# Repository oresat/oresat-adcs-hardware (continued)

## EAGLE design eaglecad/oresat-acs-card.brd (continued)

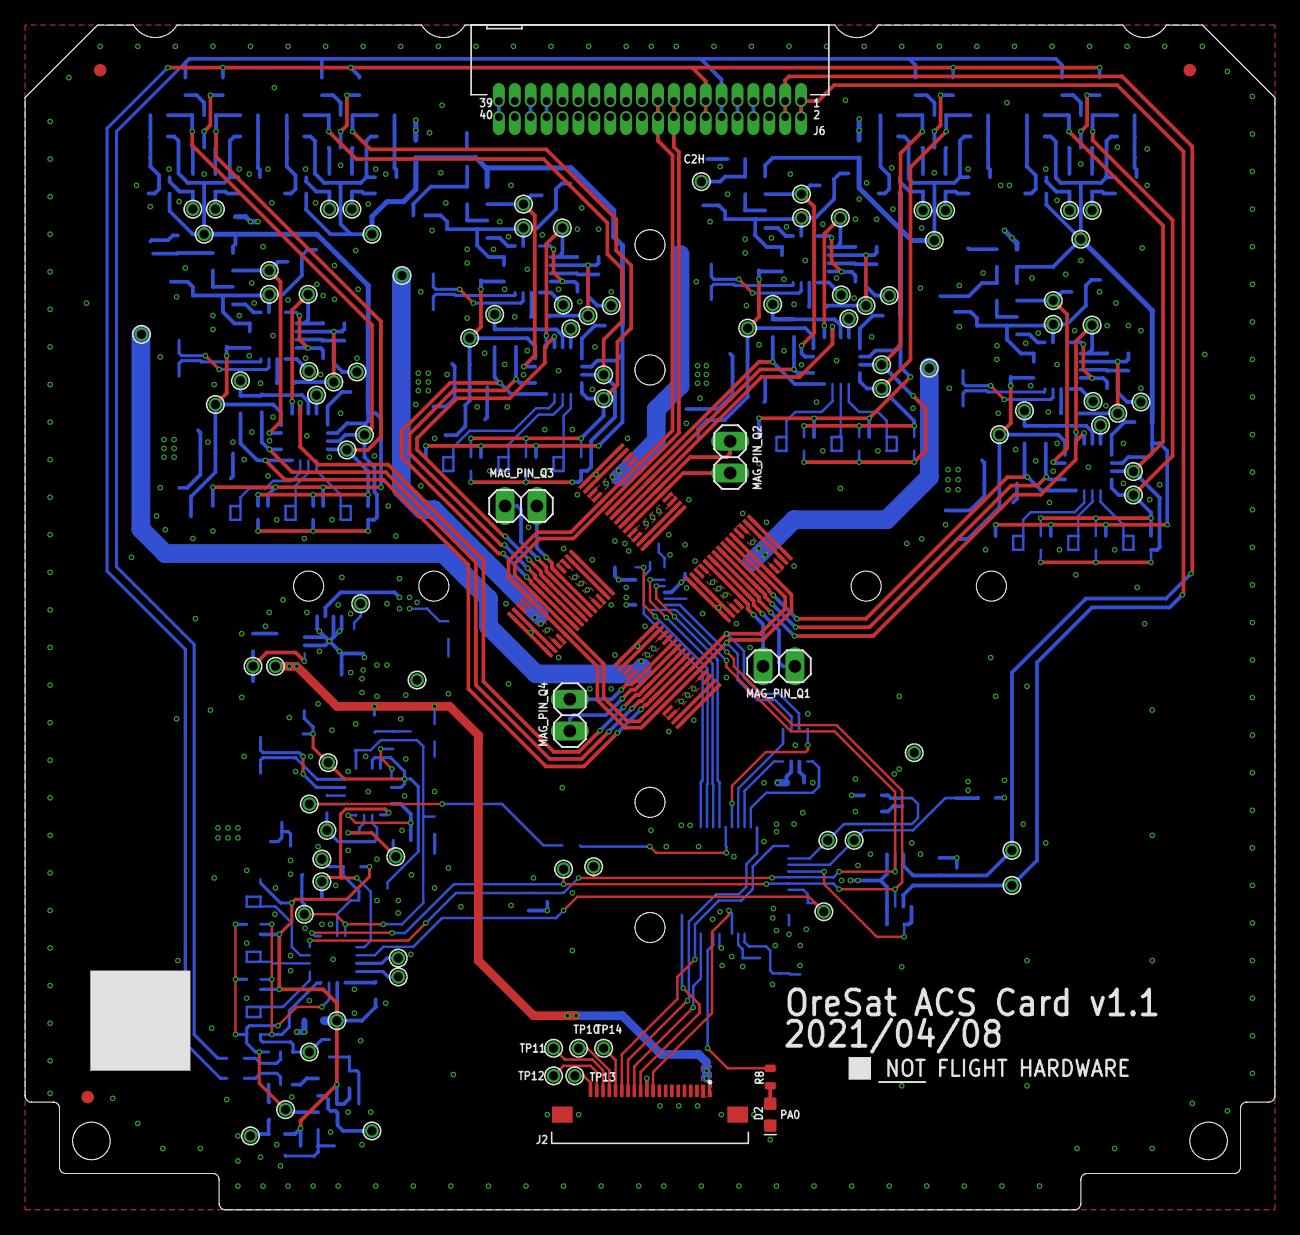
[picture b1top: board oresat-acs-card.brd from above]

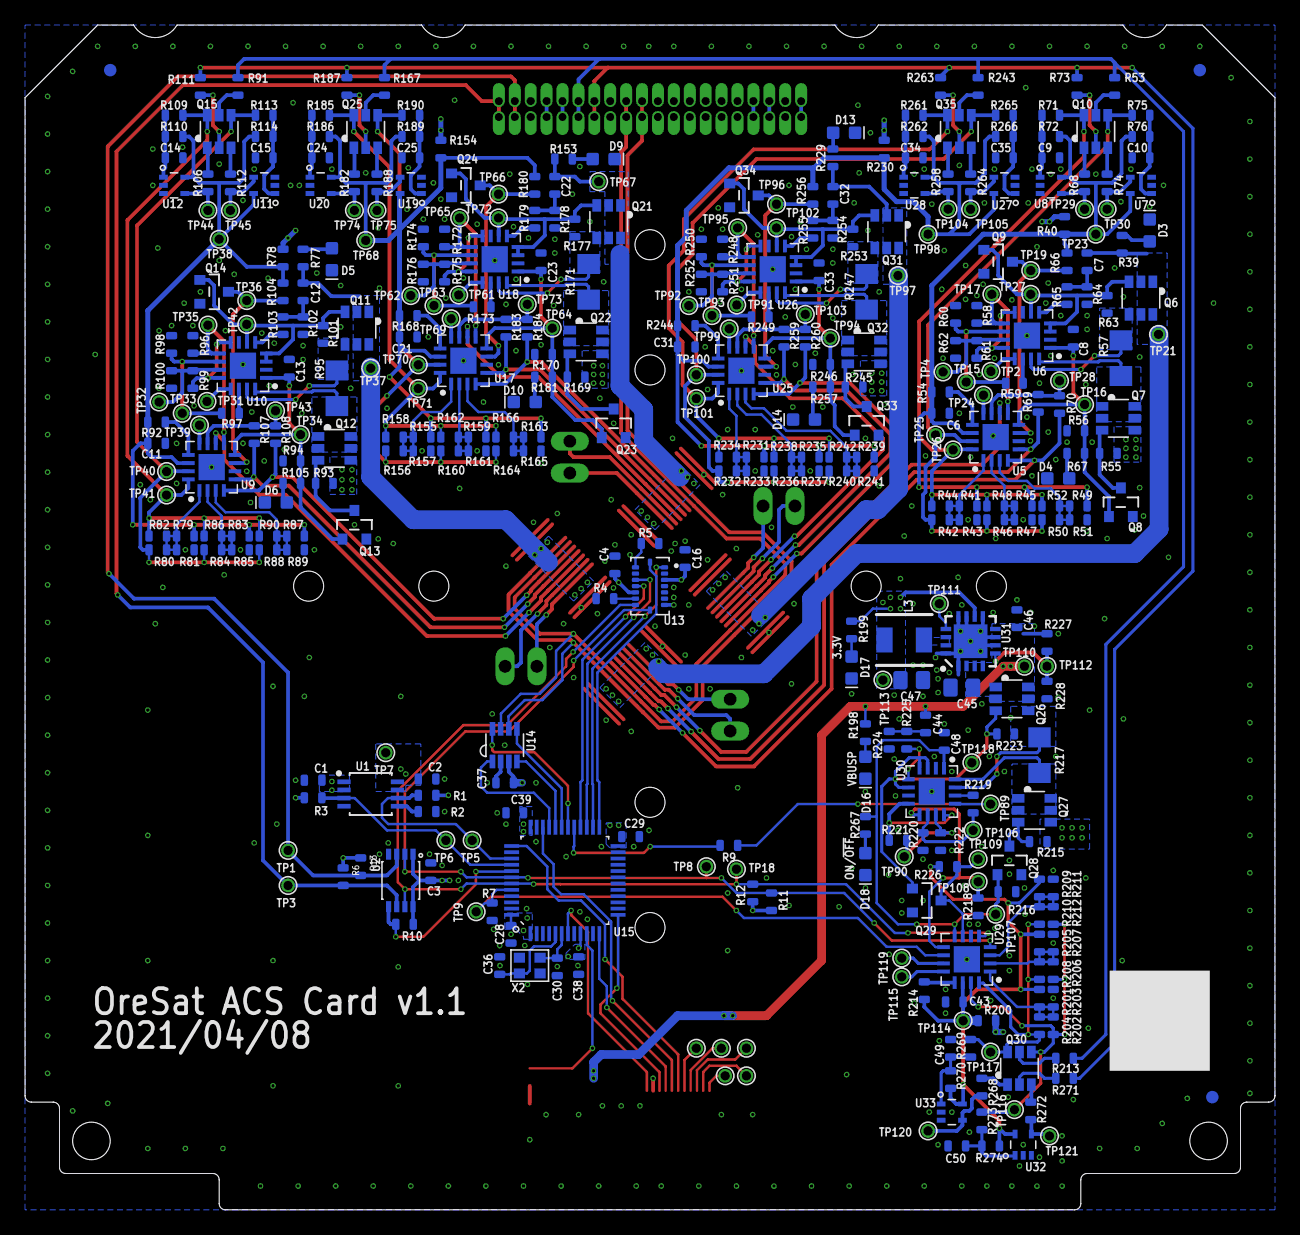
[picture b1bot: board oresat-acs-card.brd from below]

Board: 4 copper layers, 99.8 x 94.6 mm, 418 parts (389 on the bottom side), 242 nets.

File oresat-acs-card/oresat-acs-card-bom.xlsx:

Bill Of Materials for OreSat ACS Card
source file: oresat-acs-card.sch
Last modified: 2020/09/21
PCB version: 1.1 |  |  | P/DNP = | Place/Do Not Place (DNP is for final production boards)
BOM revision: 2 |  |  | Generic = | Any generic part with the same characteristics are OK (e.g., bypass cap)
Cnt | Part References | P/DNP | Mfg | Mfg PN | Description | Generic | DIS | DPN
10 | R59, R61, R97, R99, R173, R175, R219, R221, R249, R251 | P | Yageo | RC0603JR-070RL | RES SMD 0 OHM JUMPER 1/10W 0603 | Y | Digi-Key | 311-0.0GRCT-ND
5 | R40, R78, R154, R200, R230 | P | Yageo | RC0603FR-0710RL | RES SMD 10 OHM 1% 1/10W 0603 | Y | Digi-Key | 311-10.0HRCT-ND
10 | R53, R73, R91, R111, R167, R187, R213, R243, R263, R271 | P | Yageo | RC0603FR-07100RL | RES SMD 100 OHM 1% 1/10W 0603 | Y | Digi-Key | 311-100HRCT-ND
5 | R57, R95, R171, R217, R247 | P | Stackpole | CSR1206FTR100 | RES 0.1 OHM 1% 1/2W 1206 | Y | Digi-Key | CSR1206FTR100CT-ND
10 | C6, C11, C21, C28, C29, C31, C37, C38, C39, C43 | P | Samsung | CL10B104KB8NNNL | CAP CER 0.1UF 50V X7R 0603 | Y | Digi-Key | 1276-CL10B104KB8NNNLCT-ND
40 | R1, R3, R4, R5, R6, R7, R9, R10, R13, R54, R55, R56, R58, R63, R66, R92, R93, R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 | P | Yageo | RC0603FR-0710KL | RES SMD 10K OHM 1% 1/10W 0603 | Y | Digi-Key | 311-10.0KHRCT-ND
1 | C45 | P | Samsung | CL21B106KOQNNNG | CAP CER 10UF 16V X7R 0805 | Y | Digi-Key | 1276-6472-1-ND
1 | X2 | P | ECS Inc. | ECS-160-10-36Q-ES-TR | 16MHz ±30ppm Crystal 10pF 80 Ohms | Y | Digi-Key | XC2181CT-ND
10 | R72, R76, R110, R114, R186, R190, R262, R266, R270, R274 | P | Yageo | RC0603FR-071ML | RES SMD 1M OHM 1% 1/10W 0603 | Y | Digi-Key | 311-1.00MHRCT-ND
21 | C1, C2, C3, C4, C8, C9, C10, C13, C14, C15, C16, C23, C24, C25, C33, C34, C35, 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 | P | Yageo | CC0603KRX7R7BB105 | CAP CER 1UF 16V X7R 0603 | Y | Digi-Key | 311-1446-1-ND
14 | R8, R11, R12, R39, R67, R77, R105, R153, R181, R198, R199, R229, R257, R267 | P | TE Connectivity | CRGCQ0603F2K7 | RES CRGCQ 0603 2K7 1% | Y | Digi-Key | A129693CT-ND
2 | C30, C36 | P | Samsung | CL10C200JB8NNNC | CAP CER 20PF 50V C0G/NP0 0603 | Y | Digi-Key | 1276-1187-1-ND
1 | C47 | P | Murata | GRM21BD71A226ME44L | CAP CER 22UF 10V X7T 0805 | Y | Digi-Key | 490-9959-1-ND
1 | R2 | P | Yageo | RC0603FR-0723K7L | RES SMD 23.7K OHM 1% 1/10W 0603 | Y | Digi-Key | 311-23.7KHRCT-ND
10 | R71, R75, R109, R113, R185, R189, R261, R265, R269, R273 | P | Vishay | MCT06030C3303FP000 | RES SMD 330K OHM 1% 1/8W 0603 | Y | Digi-Key | 749-1638-1-ND
8 | R69, R70, R107, R108, R183, R184, R259, R260 | P | Yageo | RC0603FR-0747KL | RES SMD 47K OHM 1% 1/10W 0603 | Y | Digi-Key | 311-47.0KHRCT-ND
1 | L3 | P | ECS | ECS-MPI4040R4-6R8-R | FIXED IND 6.8UH 2.4A 91 MOHM SMD | N | Digi-Key | XC2337CT-ND
10 | R68, R74, R106, R112, R182, R188, R258, R264, R268, R272 | P | Yageo | RC0603FR-07665KL | RES SMD 665K OHM 1% 1/10W 0603 | Y | Digi-Key | 311-665KHRCT-ND
6 | D2, D4, D6, D10, D14, D18 | P | Inolux | IN-S63AT5A | LED AMBER CLEAR 0603 SMD | Y | Digi-Key | 1830-1064-1-ND
1 | U13 | P | Bosch Sensortec | BMI088 | ACCELEROMETER 16LGA | N | Digi-Key | 828-1082-1-ND
5 | Q10, Q15, Q25, Q30, Q35 | P | Diodes Inc | DMP2240UDM | MOSFET 2P-CH 20V 2A SOT-26 | N | Digi-Key | DMP2240UDMDICT-ND
6 | D3, D5, D9, D13, D16, D17 | P | Rohm | SML-E12M8WT86 | LED GREEN DIFFUSED 0603 SMD | Y | Digi-Key | 511-1584-1-ND
1 | J6 | P | Samtec | TFM-120-01-L-D-RA | J-SAMTEC-TFM-120-X1-XXX-D-RA | N | Digi-Key | SAM10145-ND
1 | U2 | P | Linear | LTC4300A-1IMS8#TRPBF | IC ACCELERATOR I2C HOTSWAP 8MSOP | N | Digi-Key | LTC4300A-1IMS8#TRPBFCT-ND
5 | U6, U10, U18, U26, U30 | P | Maxim | MAX4211FETE | Current Monitor Regulator High-Side 16-TQFN | N | Digi-Key | MAX4211FETE+-ND
5 | U5, U9, U17, U25, U29 | P | Maxim | MAX7310ATE | I/O Expander 8 I²C, SMBus 400kHz 16-TQFN | N | Digi-Key | MAX7310ATE+-ND
1 | U1 | P | Maxim | MAX892LEUA+ | Power Switch/Driver 1:1 P-Channel 250mA 8-uMAX | N | Digi-Key | MAX892LEUA+-ND
4 | QUADRANT1, QUADRANT2, QUADRANT3, QUADRANT4 | P | Molex | 0555600307 | 30 Position Connector Plug, Outer Shroud Contacts Surface Mount Gold | N | Digi-Key | WM9218CT-ND
10 | U7, U8, U11, U12, U19, U20, U27, U28, U32, U33 | P | Microchip | MIC842LYC5-TR | Comparator with Voltage Reference Push-Pull SC-70-5 | N | Digi-Key | 576-2927-1-ND
10 | Q6, Q7, Q11, Q12, Q21, Q22, Q26, Q27, Q31, Q32 | P | Diodes Inc | DMP3050LVT-7 | MOSFET-PCH-SOT23-6 | N | Digi-Key | DMP3050LVT-7DICT-ND
5 | C7, C12, C22, C32, C44 | NP |  |  | NP | Y
81 | R41, R42, R43, R44, R45, R46, R47, R48, R49, R50, R51, R52, R60, R62, R64, R65,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 | NP |  |  | NP | Y
1 | J2 | P | Wurth |  | ORESAT-DEBUG-CONNECTOR-SOLAR | N
10 | Q8, Q9, Q13, Q14, Q23, Q24, Q28, Q29, Q33, Q34 | P | Nexperia | PMV45EN2R | N-Channel 30V 4.1A (Ta) 510mW (Ta), 5W (Tc) Surface Mount TO-236AB | N | Digi-Key | 1727-2307-1-ND
1 | U15 | P | STMicroelectronics | STM32F042K6T7 | ARM® Cortex®-M0 STM32F0 Microcontroller | N | Digi-Key | 497-18516-ND
1 | U14 | P | Texas Instruments | TCAN330GDCNT | 1/1 Transceiver CANbus SOT-23-8 | N | Digi-Key | 296-44211-1-ND
1 | U31 | P | Texas Instruments | TPS62111RSAR | Buck Switching Regulator IC Positive Fixed 3.3V 1 Output 1.5A 16-VQFN Exposed P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 | N | Digi-Key | 296-37681-2-ND
VERSION INFO
 | Date | Notes
Rev
1.1r1 | 44095 | Changed 0402 components to 0603 and updated some values
1.1r0 | 44082 | BOM for 1.1r0
1.0r0 | 44036 | First BOM version

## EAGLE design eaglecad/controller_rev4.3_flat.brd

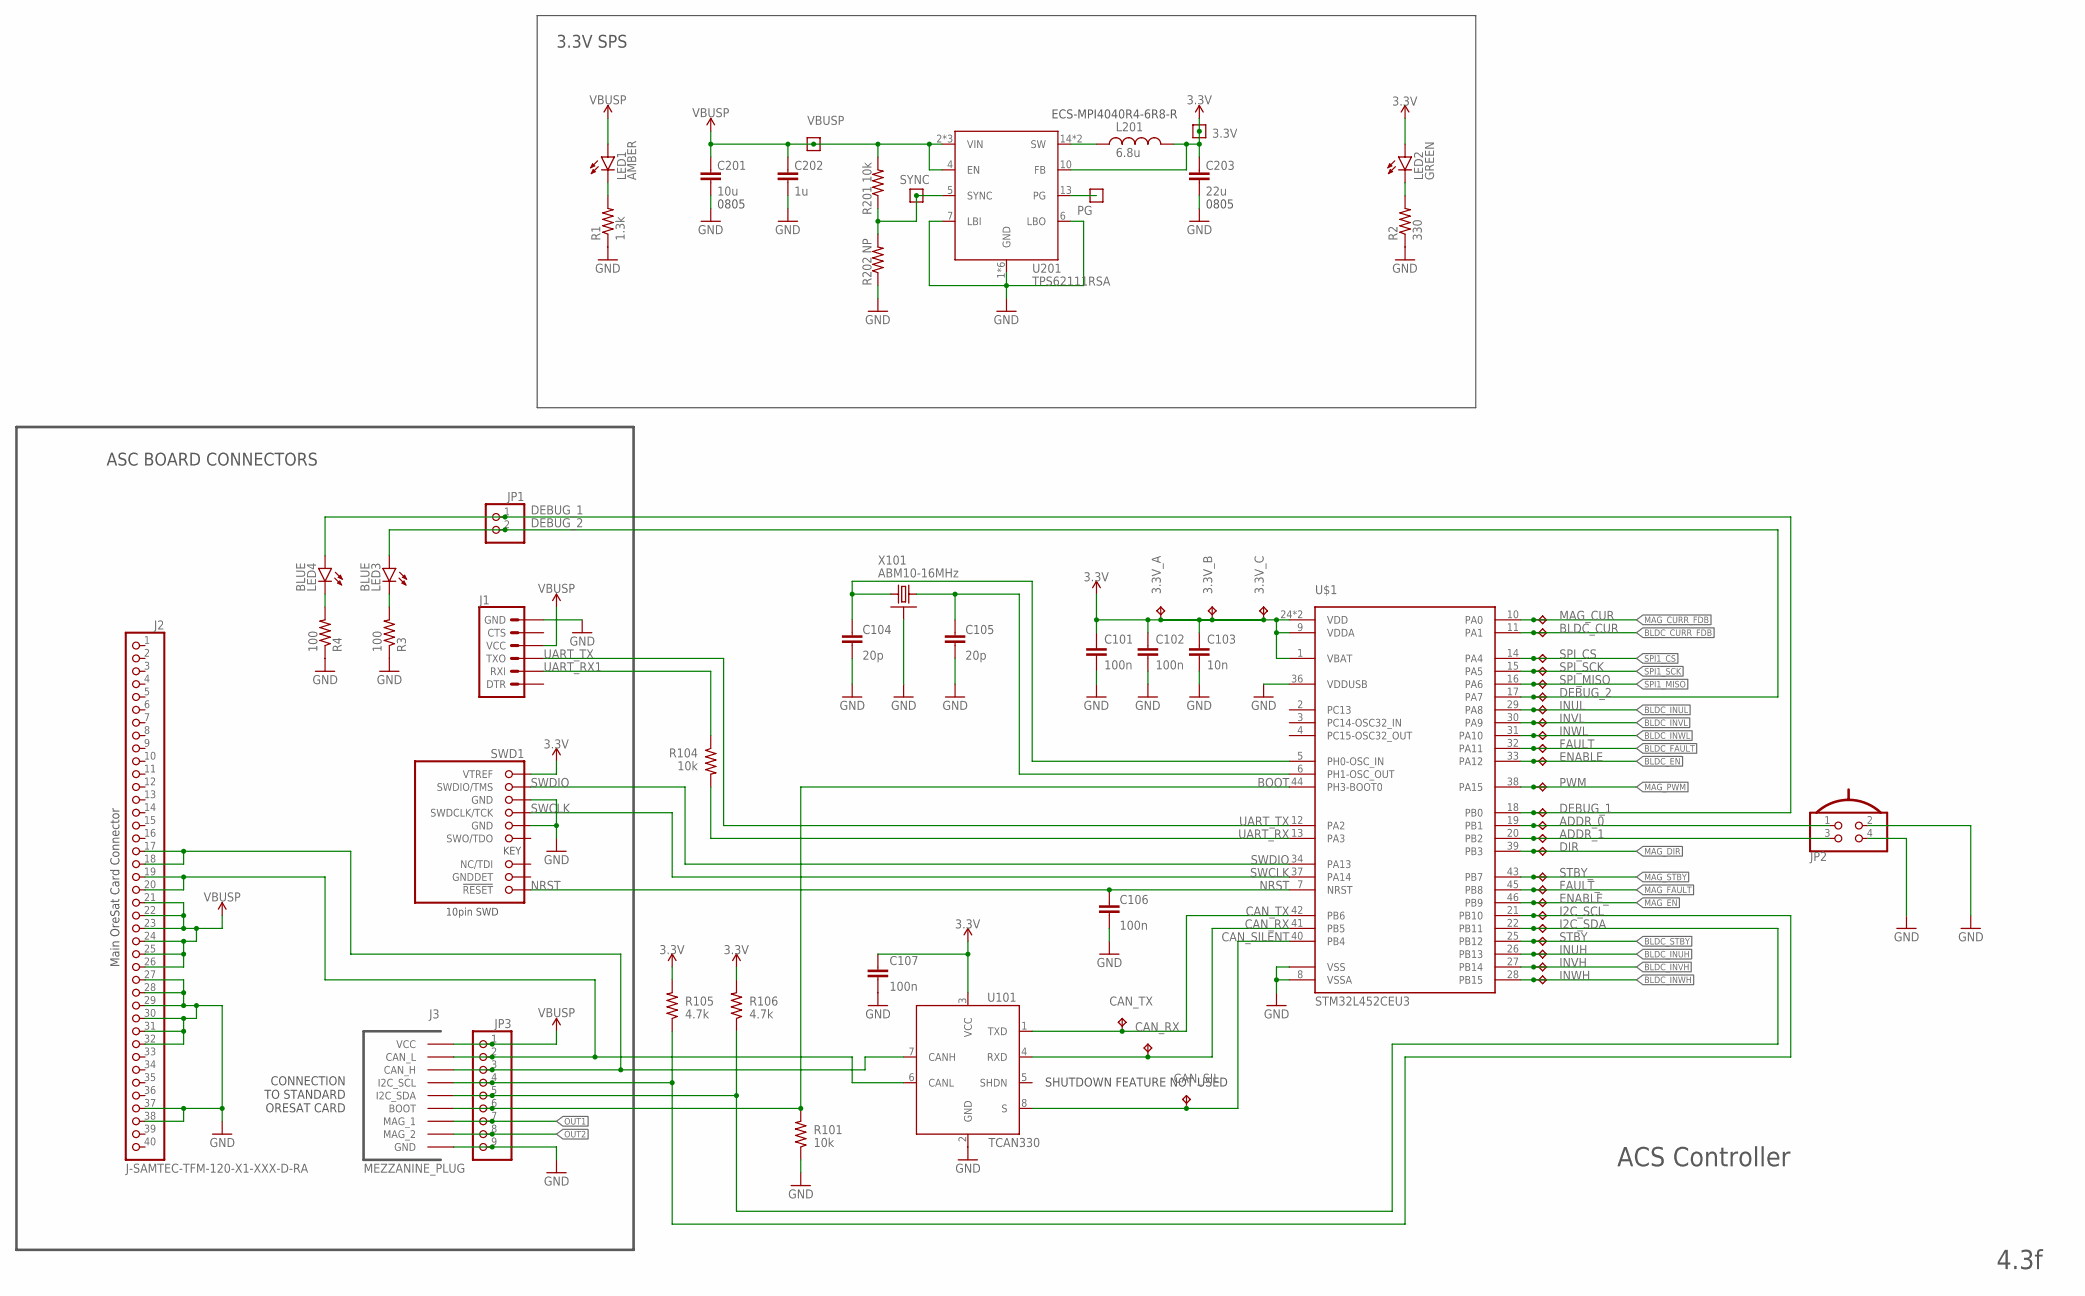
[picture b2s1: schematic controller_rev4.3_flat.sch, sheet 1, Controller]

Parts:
3.3V: TEST-POINT-LARGE-SQUARE; 1X01
3.3V_A, 3.3V_B, 3.3V_C: TEST-POINT-LARGE; 1X01
ADDR_0, ADDR_1: TEST-POINT-LARGE; 1X01
BLDC_CUR: TEST-POINT-LARGE; 1X01
C101, C102, C107: 100n; .0402-B-NOSILK; MPN CL05B104KO5NNNC
C103: 10n; .0402-B-NOSILK; MPN CL05B104KO5NNNC
C104, C105: 20p; .0402-B-NOSILK; MPN CL05C200JB51PNC
C106: 100n; .0402-B-NOSILK; MPN CL05C200JB51PNC
C201: 10u; .0805-B-NOSILK; MPN CL21B106KOQNNNG
C202: 1u; .0603-C-NOSILK; MPN CC0603KRX5R7BB105
C203: 22u; .0805-B-NOSILK; MPN GRM21BD71A226ME44L
CAN_RX: TEST-POINT-LARGE; 1X01
CAN_SIL: TEST-POINT-LARGE; 1X01
CAN_TX: TEST-POINT-LARGE; 1X01
DEBUG_1, DEBUG_2: TEST-POINT-LARGE; 1X01
DIR: TEST-POINT-LARGE; 1X01
ENABLE: TEST-POINT-LARGE; 1X01
ENABLE_: TEST-POINT-LARGE; 1X01
FAULT: TEST-POINT-LARGE; 1X01
FAULT_: TEST-POINT-LARGE; 1X01
I2C_SCL, I2C_SDA: TEST-POINT-LARGE; 1X01
INUH: TEST-POINT-LARGE; 1X01
INUL: TEST-POINT-LARGE; 1X01
INVH: TEST-POINT-LARGE; 1X01
INVL: TEST-POINT-LARGE; 1X01
INWH: TEST-POINT-LARGE; 1X01
INWL: TEST-POINT-LARGE; 1X01
J1: 6_PIN_SERIAL_TARGETSILK; 6_PIN_SERIAL_TARGET_SIDE_W_SILK
J2: J-SAMTEC-TFM-120-X1-XXX-D-RA; MFG_PN TFM-120-01-L-D-RA
J3: MEZZANINE_PLUG
JP1: PINHD-1X2; 1X02
JP2: PINHD-2X2; 2X02; MFG_PN M20-9760246
JP3: PINHD-1X9; 1X09
L201: 6.8u; ECS-MPI4040; MPN ECS-MPI4040R4-6R8-R
LED1: AMBER; CHIPLED_0603
LED2: GREEN; CHIPLED_0603
LED3, LED4: BLUE; CHIPLED_0603
MAG_CUR: TEST-POINT-LARGE; 1X01
PG: TEST-POINT-LARGE-SQUARE; 1X01
PWM: TEST-POINT-LARGE; 1X01
R1: 1.3k; .0402-B-NOSILK
R2: 330; .0402-B-NOSILK
R3, R4: 100; .0402-B-NOSILK
R101, R104: 10k; .0402-B-NOSILK; MPN RC1005F6653CS
R105, R106: 4.7k; .0402-B-NOSILK; MPN RC1005F6653CS
R201: 10k; .0603-C-NOSILK; MPN RNCP0603FTD10K0
R202: NP; .0603-C-NOSILK; MPN RC1005F6653CS
SPI_CS: TEST-POINT-LARGE; 1X01
SPI_MISO: TEST-POINT-LARGE; 1X01
SPI_SCK: TEST-POINT-LARGE; 1X01
STBY: TEST-POINT-LARGE; 1X01
STBY_: TEST-POINT-LARGE; 1X01
SWD1: 1.27MM-SWD-CONNECTOR; 1.27MM_2X5
SYNC: TEST-POINT-LARGE-SQUARE; 1X01
U101: TCAN330; SOT23-8_TI-DCN; MPN TCAN330GDCNT
U201: TPS62111RSA; S-PVQFN-16; MPN TPS62111RSA
U$1: STM32L452CEU3; QFPN-48
VBUSP: TEST-POINT-LARGE-SQUARE; 1X01
X101: ABM10-16MHz; CRYSTAL_2.5X2; MPN ECS-160-10-36Q-ES-TR

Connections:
3.3V: 3.3V.1, 3.3V_A.1, 3.3V_B.1, 3.3V_C.1, C101.1, C102.1, C103.1, C107.1, C203.1, L201.2, LED2.A, R105.2, R106.2, SWD1.VTREF, U101.3 (VCC), U201.10 (FB), U$1.1 (VBAT), U$1.9 (VDDA), U$1.24 (VDD), U$1.48 (VDD); also elsewhere on the board
ADDR_0: ADDR_0.1, JP2.1, U$1.19 (PB1)
ADDR_1: ADDR_1.1, JP2.3, U$1.20 (PB2)
BLDC_CURR_FDB: BLDC_CUR.1, U$1.11 (PA1); also elsewhere on the board
BLDC_EN: ENABLE.1, U$1.33 (PA12); also elsewhere on the board
BLDC_FAULT: FAULT.1, U$1.32 (PA11); also elsewhere on the board
BLDC_INUH: INUH.1, U$1.26 (PB13); also elsewhere on the board
BLDC_INUL: INUL.1, U$1.29 (PA8); also elsewhere on the board
BLDC_INVH: INVH.1, U$1.27 (PB14); also elsewhere on the board
BLDC_INVL: INVL.1, U$1.30 (PA9); also elsewhere on the board
BLDC_INWH: INWH.1, U$1.28 (PB15); also elsewhere on the board
BLDC_INWL: INWL.1, U$1.31 (PA10); also elsewhere on the board
BLDC_STBY: STBY.1, U$1.25 (PB12); also elsewhere on the board
BOOT: J3.P$9 (BOOT), J3.P$22 (BOOT), JP3.6, R101.2, U$1.44 (PH3-BOOT0)
CAN_H: J2.17, J2.18, J3.P$6 (CAN_H), J3.P$25 (CAN_H), JP3.3, U101.7 (CANH)
CAN_L: J2.19, J2.20, J3.P$5 (CAN_L), J3.P$26 (CAN_L), JP3.2, U101.6 (CANL)
CAN_RX: CAN_RX.1, U101.4 (RXD), U$1.41 (PB5)
CAN_SILENT: CAN_SIL.1, U101.8 (S), U$1.40 (PB4)
CAN_TX: CAN_TX.1, U101.1 (TXD), U$1.42 (PB6)
CLK1: C104.1, U$1.5 (PH0-OSC_IN), X101.3 (2)
CLK2: C105.1, U$1.6 (PH1-OSC_OUT), X101.1
DEBUG_1: DEBUG_1.1, JP1.1, LED4.A, U$1.18 (PB0)
DEBUG_2: DEBUG_2.1, JP1.2, LED3.A, U$1.17 (PA7)
GND: C101.2, C102.2, C103.2, C104.2, C105.2, C106.2, C107.2, C201.2, C202.2, C203.2, J1.P$6 (GND), J2.27, J2.28, J2.29, J2.30, J2.31, J2.32, J2.37, J2.38, J3.P$1 (GND), J3.P$2 (GND), J3.P$14 (GND), J3.P$15 (GND), J3.P$16 (GND), J3.P$17 (GND), J3.P$29 (GND), J3.P$30 (GND), JP2.2, JP2.4, JP3.9, R1.1, R2.1, R3.1, R4.1, R101.1, R202.1, SWD1.GND, SWD1.GND@2 (GND), U101.2 (GND), U201.1 (GND), U201.6 (LBO), U201.7 (LBI), U201.9 (GND), U201.11 (GND), U201.12 (GND), U201.16 (GND), U201.PAD (GND), U$1.8 (VSSA), U$1.23 (VSS), U$1.35 (VSS), U$1.36 (VDDUSB), U$1.47 (VSS), U$1.EPAD (VSS), X101.2 (SHIELD), X101.4 (SHIELD); also elsewhere on the board
I2C_SCL: I2C_SCL.1, J3.P$7 (I2C_SCL), J3.P$24 (I2C_SCL), JP3.4, R105.1, U$1.21 (PB10)
I2C_SDA: I2C_SDA.1, J3.P$8 (I2C_SDA), J3.P$23 (I2C_SDA), JP3.5, R106.1, U$1.22 (PB11)
MAG_CURR_FDB: MAG_CUR.1, U$1.10 (PA0); also elsewhere on the board
MAG_DIR: DIR.1, U$1.39 (PB3); also elsewhere on the board
MAG_EN: ENABLE_.1, U$1.46 (PB9); also elsewhere on the board
MAG_FAULT: FAULT_.1, U$1.45 (PB8); also elsewhere on the board
MAG_PWM: PWM.1, U$1.38 (PA15); also elsewhere on the board
MAG_STBY: STBY_.1, U$1.43 (PB7); also elsewhere on the board
unnamed: LED4.C, R4.2
unnamed: LED3.C, R3.2
unnamed: LED1.C, R1.2
unnamed: LED2.C, R2.2
NRST: C106.1, SWD1.!RESET, U$1.7 (NRST)
OUT1: J3.P$10 (MAG_1), J3.P$21 (MAG_1), JP3.7; also elsewhere on the board
OUT2: J3.P$11 (MAG_2), J3.P$20 (MAG_2), JP3.8; also elsewhere on the board
SPI1_CS: SPI_CS.1, U$1.14 (PA4); also elsewhere on the board
SPI1_MISO: SPI_MISO.1, U$1.16 (PA6); also elsewhere on the board
SPI1_SCK: SPI_SCK.1, U$1.15 (PA5); also elsewhere on the board
SWCLK: SWD1.SWDCLK (SWDCLK/TCK), U$1.37 (PA14)
SWDIO: SWD1.SWDIO (SWDIO/TMS), U$1.34 (PA13)
TPS62111-PG2: PG.1, U201.13 (PG)
TPS62111-SYNC2: R201.1, R202.2, SYNC.1, U201.5 (SYNC)
TPS62111_SW1: L201.1, U201.14 (SW), U201.15 (SW)
UART_RX: R104.2, U$1.13 (PA3)
UART_RX1: J1.P$3 (RXI), R104.1
UART_TX: J1.P$2 (TXO), U$1.12 (PA2)
VBUSP: C201.1, C202.1, J1.P$4 (VCC), J2.21, J2.22, J2.23, J2.24, J2.25, J2.26, J3.P$3 (VCC), J3.P$4 (VCC), J3.P$12 (VCC), J3.P$13 (VCC), J3.P$18 (VCC), J3.P$19 (VCC), J3.P$27 (VCC), J3.P$28 (VCC), JP3.1, LED1.A, R201.2, U201.2 (VIN), U201.3 (VIN), U201.4 (EN), U201.8 (VIN), VBUSP.1; also elsewhere on the board

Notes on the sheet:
ACS Controller
4.3f
3.3V SPS
CONNECTION TO STANDARD ORESAT CARD
ASC BOARD CONNECTORS
SHUTDOWN FEATURE NOT USED
Main OreSat Card Connector
0805
ECS-MPI4040R4-6R8-R

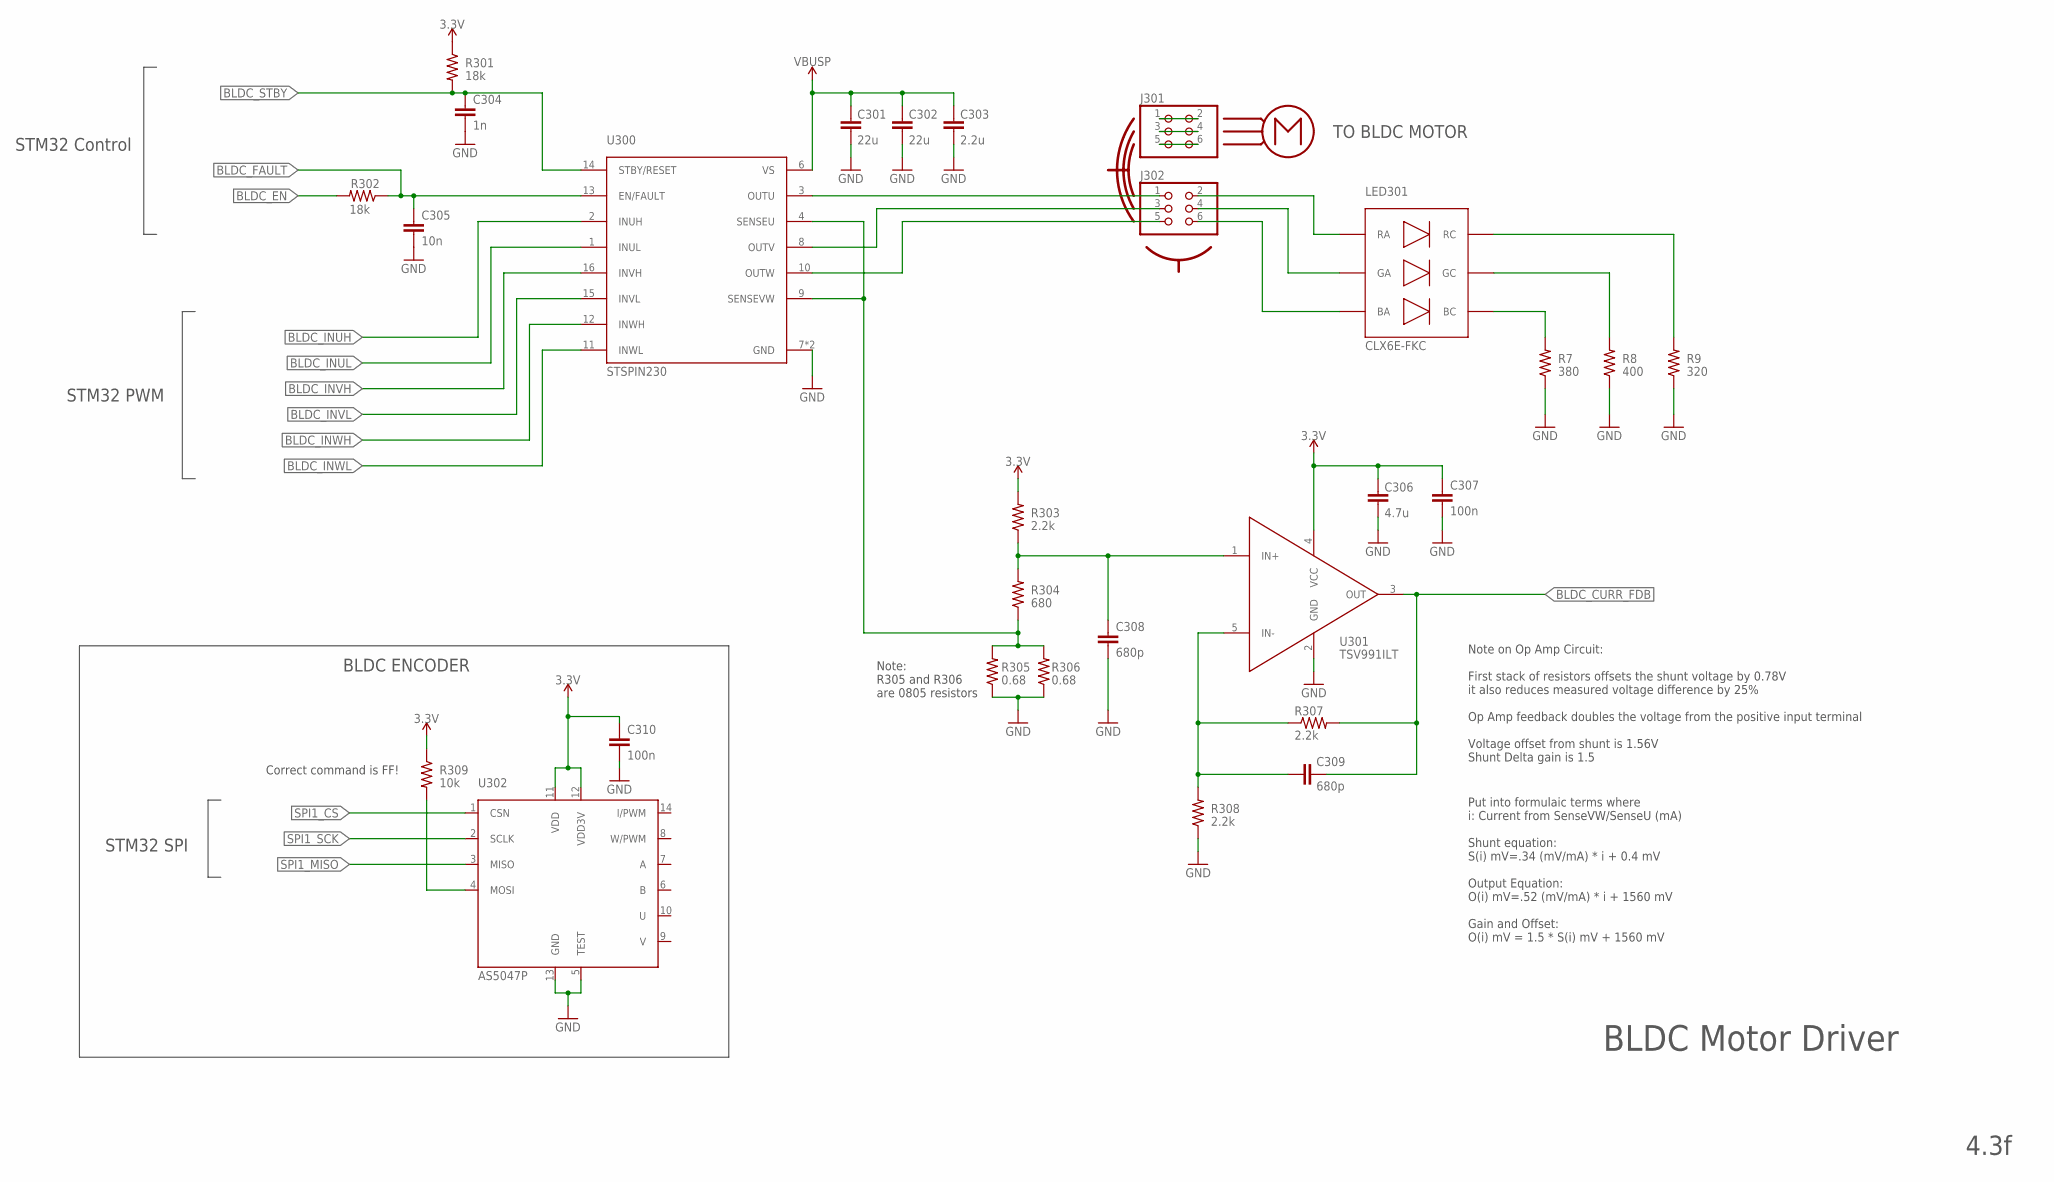
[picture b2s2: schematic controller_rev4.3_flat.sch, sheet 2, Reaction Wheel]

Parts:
C301, C302: 22u; .0603-B-NOSILK; MPN CL05B104KO5NNNC
C303: 2.2u; .0603-B-NOSILK; MPN CL05B104KO5NNNC
C304: 1n; .0402-B-NOSILK; MPN CL05B104KO5NNNC
C305: 10n; .0402-B-NOSILK; MPN CL05B104KO5NNNC
C306: 4.7u; .0603-B-NOSILK; MPN CL05B104KO5NNNC
C307, C310: 100n; .0402-B-NOSILK; MPN CL05B104KO5NNNC
C308, C309: 680p; .0402-B-NOSILK; MPN CL05B104KO5NNNC
J301, J302: PINHD-2X3; 2X03
LED301: CLX6E-FKC
R7: 380; .0402-B-NOSILK; MPN RC1005F6653CS
R8: 400; .0402-B-NOSILK; MPN RC1005F6653CS
R9: 320; .0402-B-NOSILK; MPN RC1005F6653CS
R301, R302: 18k; .0402-B-NOSILK; MPN RC1005F6653CS
R303, R307, R308: 2.2k; .0402-B-NOSILK; MPN RC1005F6653CS
R304: 680; .0402-B-NOSILK; MPN RC1005F6653CS
R305, R306: 0.68; .0805-B-NOSILK
R309: 10k; .0402-B-NOSILK; MPN RC1005F6653CS
U300: STSPIN230; VFQPN
U301: TSV991ILT; SOT23-5
U302: AS5047P; TSSOP14

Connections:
3.3V: C306.1, C307.1, C310.1, R301.1, R303.2, R309.1, U301.4 (VCC), U302.11 (VDD), U302.12 (VDD3V); also elsewhere on the board
AS5047_MOSI: R309.2, U302.4 (MOSI)
BLDC_CURR_FDB: C309.1, R307.2, U301.3 (OUT); also elsewhere on the board
BLDC_EN: R302.2; also elsewhere on the board
BLDC_FAULT: C305.1, R302.1, U300.13 (EN/FAULT); also elsewhere on the board
BLDC_INUH: U300.2 (INUH); also elsewhere on the board
BLDC_INUL: U300.1 (INUL); also elsewhere on the board
BLDC_INVH: U300.16 (INVH); also elsewhere on the board
BLDC_INVL: U300.15 (INVL); also elsewhere on the board
BLDC_INWH: U300.12 (INWH); also elsewhere on the board
BLDC_INWL: U300.11 (INWL); also elsewhere on the board
BLDC_STBY: C304.1, R301.2, U300.14 (STBY/RESET); also elsewhere on the board
B_IN+: C308.1, R303.1, R304.2, U301.1 (IN+)
B_IN-: C309.2, R307.1, R308.2, U301.5 (IN-)
GND: C301.2, C302.2, C303.2, C304.2, C305.2, C306.2, C307.2, C308.2, C310.2, R7.1, R8.1, R9.1, R305.1, R306.1, R308.1, U300.7 (GND), U300.EPAD (GND), U301.2 (GND), U302.5 (TEST), U302.13 (GND); also elsewhere on the board
unnamed: J302.2, LED301.P$4 (RA)
unnamed: J302.4, LED301.P$5 (GA)
unnamed: J302.6, LED301.P$6 (BA)
unnamed: J301.5, J301.6
unnamed: J301.3, J301.4
unnamed: J301.1, J301.2
unnamed: LED301.P$1 (BC), R7.2
unnamed: LED301.P$2 (GC), R8.2
unnamed: LED301.P$3 (RC), R9.2
SENSE_BLDC: R304.1, R305.2, R306.2, U300.4 (SENSEU), U300.9 (SENSEVW)
SPI1_CS: U302.1 (CSN); also elsewhere on the board
SPI1_MISO: U302.3 (MISO); also elsewhere on the board
SPI1_SCK: U302.2 (SCLK); also elsewhere on the board
U: J302.1, U300.3 (OUTU)
V: J302.3, U300.8 (OUTV)
VBUSP: C301.1, C302.1, C303.1, U300.6 (VS); also elsewhere on the board
W: J302.5, U300.10 (OUTW)

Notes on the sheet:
TO BLDC MOTOR
BLDC Motor Driver
STM32 PWM
STM32 Control
Correct command is FF!
STM32 SPI
BLDC ENCODER
4.3f
Note on Op Amp Circuit: First stack of resistors offsets the shunt voltage by 0.78V it also reduces measured voltage difference by 25% Op Amp feedback doubles the voltage from the positive input terminal Voltage offset from shunt is 1.56V Shunt Delta gain is 1.5
Put into formulaic terms where i: Current from SenseVW/SenseU (mA) Shunt equation: S(i) mV=.34 (mV/mA) * i + 0.4 mV Output Equation: O(i) mV=.52 (mV/mA) * i + 1560 mV Gain and Offset: O(i) mV = 1.5 * S(i) mV + 1560 mV
Note: R305 and R306 are 0805 resistors

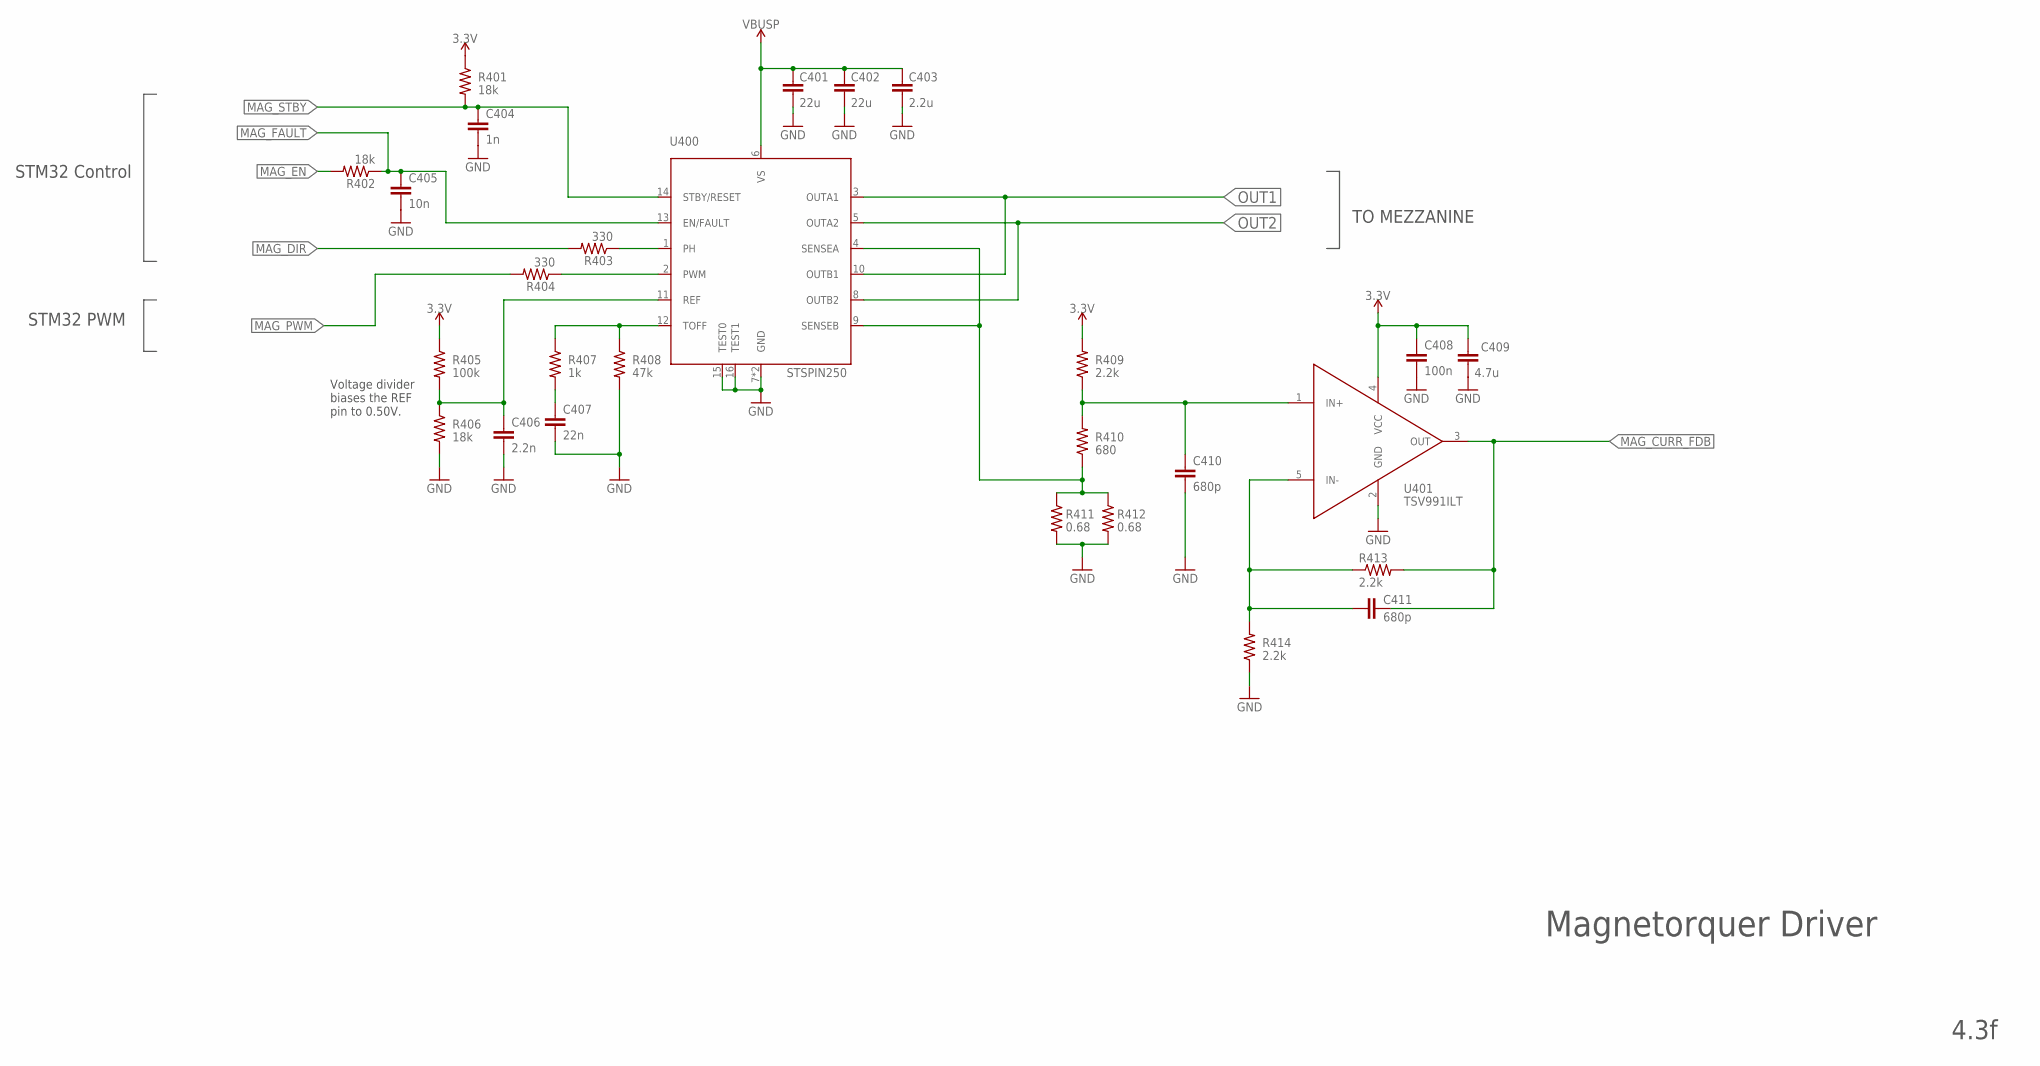
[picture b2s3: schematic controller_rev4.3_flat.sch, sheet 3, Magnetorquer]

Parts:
C401, C402: 22u; .0603-B-NOSILK; MPN CL05B104KO5NNNC
C403: 2.2u; .0603-B-NOSILK; MPN CL05B104KO5NNNC
C404: 1n; .0402-B-NOSILK; MPN CL05B104KO5NNNC
C405: 10n; .0402-B-NOSILK; MPN CL05B104KO5NNNC
C406: 2.2n; .0402-B-NOSILK; MPN CL05B104KO5NNNC
C407: 22n; .0402-B-NOSILK; MPN CL05B104KO5NNNC
C408: 100n; .0402-B-NOSILK; MPN CL05B104KO5NNNC
C409: 4.7u; .0603-B-NOSILK; MPN CL05B104KO5NNNC
C410, C411: 680p; .0402-B-NOSILK; MPN CL05B104KO5NNNC
R401, R402, R406: 18k; .0402-B-NOSILK; MPN RC1005F6653CS
R403, R404: 330; .0402-B-NOSILK; MPN RC1005F6653CS
R405: 100k; .0402-B-NOSILK; MPN RC1005F6653CS
R407: 1k; .0402-B-NOSILK; MPN RC1005F6653CS
R408: 47k; .0402-B-NOSILK; MPN RC1005F6653CS
R409, R413, R414: 2.2k; .0402-B-NOSILK; MPN RC1005F6653CS
R410: 680; .0402-B-NOSILK; MPN RC1005F6653CS
R411, R412: 0.68; .0805-B-NOSILK
U400: STSPIN250; VFQPN
U401: TSV991ILT; SOT23-5

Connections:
3.3V: C408.1, C409.1, R401.1, R405.1, R409.2, U401.4 (VCC); also elsewhere on the board
250_REF: C406.1, R405.2, R406.1, U400.11 (REF)
250_TOFF: R407.1, R408.1, U400.12 (TOFF)
GND: C401.2, C402.2, C403.2, C404.2, C405.2, C406.2, C407.2, C408.2, C409.2, C410.2, R406.2, R408.2, R411.2, R412.2, R414.1, U400.7 (GND), U400.15 (TEST0), U400.16 (TEST1), U400.EPAD (GND), U401.2 (GND); also elsewhere on the board
MAG_CURR_FDB: C411.1, R413.2, U401.3 (OUT); also elsewhere on the board
MAG_DIR: R403.2; also elsewhere on the board
MAG_EN: R402.2; also elsewhere on the board
MAG_FAULT: C405.1, R402.1, U400.13 (EN/FAULT); also elsewhere on the board
MAG_PWM: R404.2; also elsewhere on the board
MAG_STBY: C404.1, R401.2, U400.14 (STBY/RESET); also elsewhere on the board
M_IN+: C410.1, R409.1, R410.2, U401.1 (IN+)
M_IN-: C411.2, R413.1, R414.2, U401.5 (IN-)
M_PH: R403.1, U400.1 (PH)
M_PWM: R404.1, U400.2 (PWM)
OUT1: U400.3 (OUTA1), U400.10 (OUTB1); also elsewhere on the board
OUT2: U400.5 (OUTA2), U400.8 (OUTB2); also elsewhere on the board
SENSE_MAG: R410.1, R411.1, R412.1, U400.4 (SENSEA), U400.9 (SENSEB)
TOFF1: C407.1, R407.2
VBUSP: C401.1, C402.1, C403.1, U400.6 (VS); also elsewhere on the board

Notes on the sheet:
TO MEZZANINE
Magnetorquer Driver
Voltage divider biases the REF pin to 0.50V.
STM32 PWM
STM32 Control
4.3f

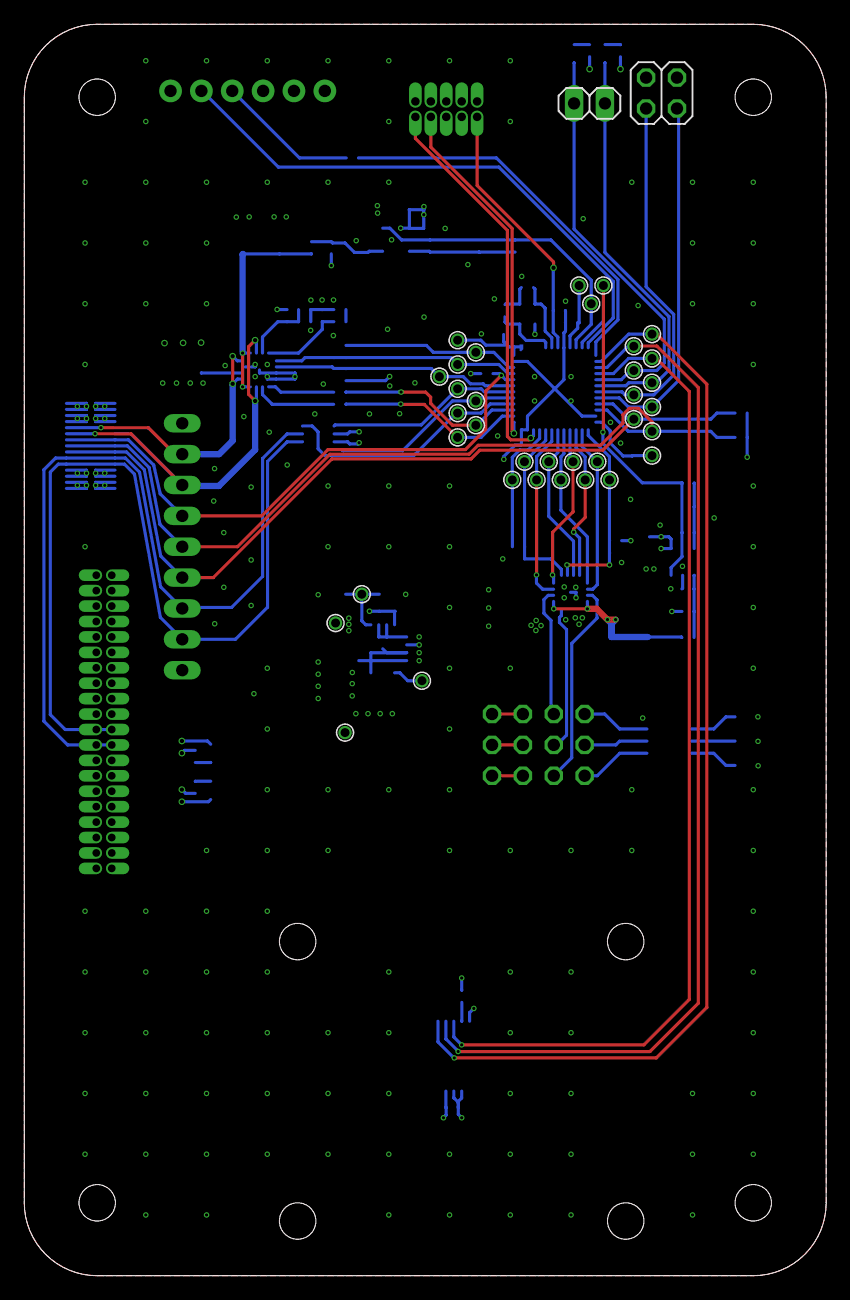
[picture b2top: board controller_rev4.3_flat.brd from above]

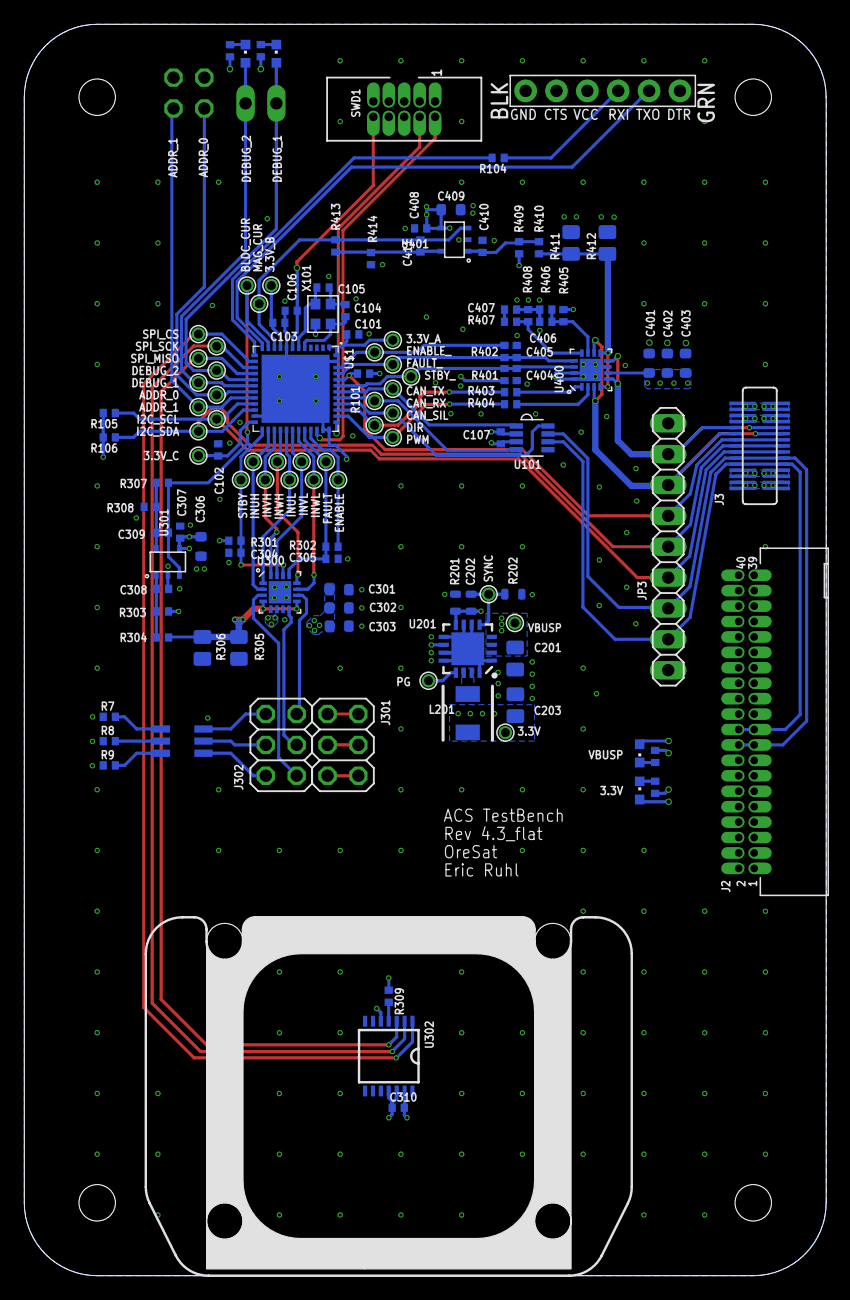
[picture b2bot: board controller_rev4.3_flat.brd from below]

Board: 4 copper layers, 66.0 x 103.0 mm, 126 parts (93 on the bottom side), 75 nets.
